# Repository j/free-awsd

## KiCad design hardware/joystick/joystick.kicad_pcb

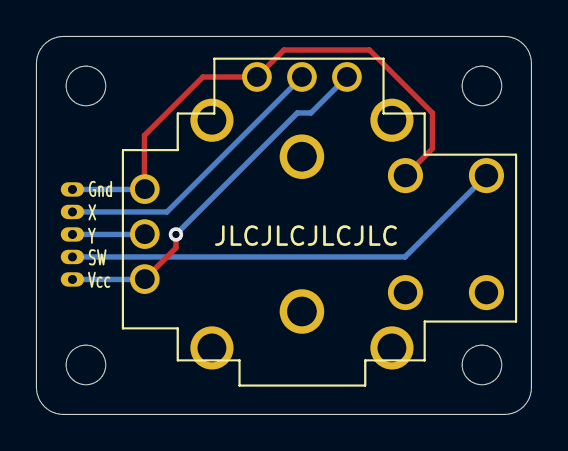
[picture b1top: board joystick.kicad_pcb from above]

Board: 2 copper layers, 27.5 x 21.0 mm, 6 parts (1 on the bottom side), 5 nets.

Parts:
H1, H2, H3, H4: MountingHole; MountingHole_2.2mm_M2
J1: Conn_01x05; Molex_PicoBlade_53047-0510_1x05_P1.25mm_Vertical
U1: RKJXV122400R

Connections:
unnamed: J1.1, U1.A13, U1.B11, U1.C1
unnamed: J1.2, U1.A12
unnamed: J1.3, U1.B12
unnamed: J1.4, U1.D1
unnamed: J1.5, U1.A11, U1.B13

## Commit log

2021-04-15 feat: init
